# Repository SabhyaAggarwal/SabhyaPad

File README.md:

# SabhyaPad

This is my own MacroPad, called **SabhyaPad**! It has 6 buttons that can easily be customized using QMK. Using it is really simple: just plug a USB-C cable into your computer, allow it to connect, and then start using it.

I made this so that my life is easier. Currently, it is configured to do this...

## Here is a [video](https://youtu.be/60F119tDTQQ) of it on YouTube!!! I accidentally put the wrong link in the demo section actually...

## BOM
|Item                    |Quantity|Remarks                                       |Unit Price 1 (INR)|Order Quantity|Order Unit Price (INR)|Order Unit Price (Est. USD)|Link To Buy                                                                                                                           |
|------------------------|--------|----------------------------------------------|------------------|--------------|----------------------|---------------------------|--------------------------------------------------------------------------------------------------------------------------------------|
|Switches                |6       |Switches of MX style.                         |₹93.18            |6             |₹93.18                |$1.00                      |https://www.mouser.in/ProductDetail/CHERRY/MX1A-L1NN?qs=F5EMLAvA7IDlALNAurZTXA%3D%3D                                                  |
|Seeed Studio Xiao RP2040|1       |Main Chip.                                    |₹464.97           |1             |₹464.97               |$4.90                      |https://www.mouser.in/ProductDetail/Seeed-Studio/102010630?qs=sqEgtWRSLJ0HHL%252BkmwiGyA%3D%3D                                        |
|Blank DSA keycaps       |6       |Blank DSA keycaps of black colour(3d printed).|₹2.13             |6             |₹12.75                |$0.13                      |Own 3d printer or print-legion                                                                                                        |
|PCB                     |1       |Main PCB.                                     |₹1112.00          |1             |₹95.25                |$1.00                      |allpcb.com                                                                                                                            |
|M3x16mm screws          |4       |Screws.                                       |₹12.27            |4             |₹49.09                |$0.51                      |https://robokits.co.in/robot-parts/nut-bolts-standoffs/mushroom-head-bolts/m3-x-16-mm-ss-bolt-precision-stainless-steel-304-moq-25-pcs|
|M3 nuts                 |4       |Nuts                                          |₹1.18             |4             |₹4.72                 |$0.05                      |https://robokits.co.in/robot-parts/nut-bolts-standoffs/nuts/m3-nuts-304-stainless-steel-moq-50-pcs                                    |

## Hardware

This is the schematic of my PCB...

And this is what my PCB design looks like...

### 3D Render of PCB

## 3D Models

Please note that I will add USB-C port after I receive the PCB and can confirm the measurements

### Case Render(SabhyaPad Case Assembled)

### Cut Case Render(SabhyaPad Case Cut)

### Final Render(no keycaps)

---

# Assembly

For assembly:
1. 3D Print the case cut file.
2. Take your soldered PCB and push it into the top part. It will click and then it will be attached.
3. Take the bottom part and put it at the bottom.
4. Use M3x16mm screws and the M3 nuts to enclose it.

# Firmware

The SabhyaPad firmware is based on **QMK Firmware** and is located in:

```text
FIRMWARE/sabhyapad
```

## Requirements

Install **QMK MSYS** from:

https://qmk.fm

After installation, open QMK MSYS and verify it is installed correctly:

```bash
qmk --version
```

## Setting Up QMK

Clone and set up QMK Firmware:

```bash
qmk setup
```

## Installing SabhyaPad

Navigate to the keyboards directory:

```bash
cd qmk_firmware/keyboards
```

Clone this repository:

```bash
git clone https://github.com/SabhyaAggarwal/SabhyaPad.git
```

## Building the Firmware

Return to the QMK root directory:

```bash
cd ../..
```

Compile the firmware:

```bash
qmk compile -kb sabhyapad -km default
```

Or:

```bash
make sabhyapad:default
```

## Firmware Output

A successful build will generate:

```text
sabhyapad_default.uf2
```

Since SabhyaPad uses an **RP2040** microcontroller, the firmware is generated in UF2 format.

## Flashing the Firmware

1. Hold the **BOOTSEL** button while plugging the keyboard into your computer.
2. A drive named **RPI-RP2** will appear.
3. Drag and drop:

```text
sabhyapad_default.uf2
```

onto the drive.

The keyboard will automatically reboot and start running the new firmware.

## Updating

Pull the latest changes:

```bash
cd qmk_firmware/keyboards/SabhyaPad
git pull
```

Rebuild:

```bash
cd ../..
qmk compile -kb sabhyapad -km default
```

## Troubleshooting

Check your QMK installation:

```bash
qmk doctor
```

Clean and rebuild:

```bash
qmk clean
qmk compile -kb sabhyapad -km default
```

List available keymaps:

```bash
qmk list-keymaps -kb sabhyapad
```

## Quick Start

```bash
qmk setup

cd qmk_firmware/keyboards
git clone https://github.com/SabhyaAggarwal/SabhyaPad.git

cd ../..

qmk compile -kb sabhyapad -km default
```

### Specifications

- MCU: RP2040
- Switches: 6 Mechanical Switches
- Firmware: QMK
- Connector: USB-C
- Firmware Format: UF2

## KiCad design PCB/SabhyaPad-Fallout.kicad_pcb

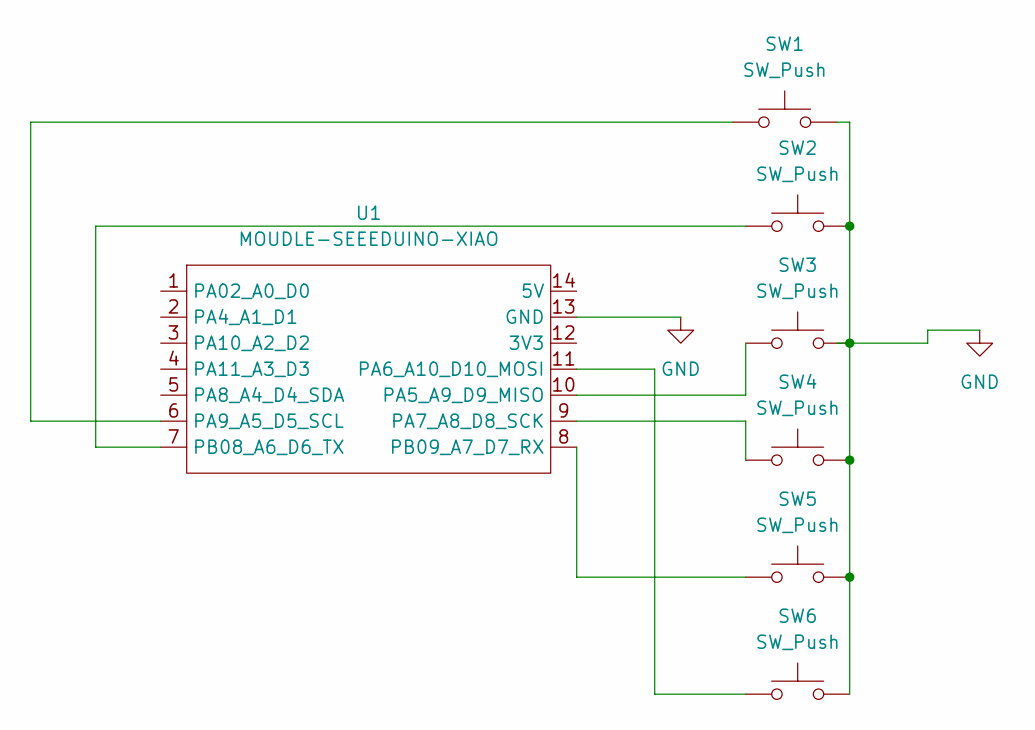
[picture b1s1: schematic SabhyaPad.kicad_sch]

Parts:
SW1, SW2, SW3, SW4, SW5, SW6: SW_Push; SW_Cherry_MX_1.00u_PCB
U1: MOUDLE-SEEEDUINO-XIAO; XIAO-Generic-Hybrid-14P-2.54-21X17.8MM

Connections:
GND: SW1.2, SW2.2, SW3.2, SW4.2, SW5.2, SW6.2, U1.13 (GND)
unnamed: SW3.1, U1.10 (PA5_A9_D9_MISO)
unnamed: SW6.1, U1.11 (PA6_A10_D10_MOSI)
unnamed: SW4.1, U1.9 (PA7_A8_D8_SCK)
unnamed: SW1.1, U1.6 (PA9_A5_D5_SCL)
unnamed: SW2.1, U1.7 (PB08_A6_D6_TX)
unnamed: SW5.1, U1.8 (PB09_A7_D7_RX)

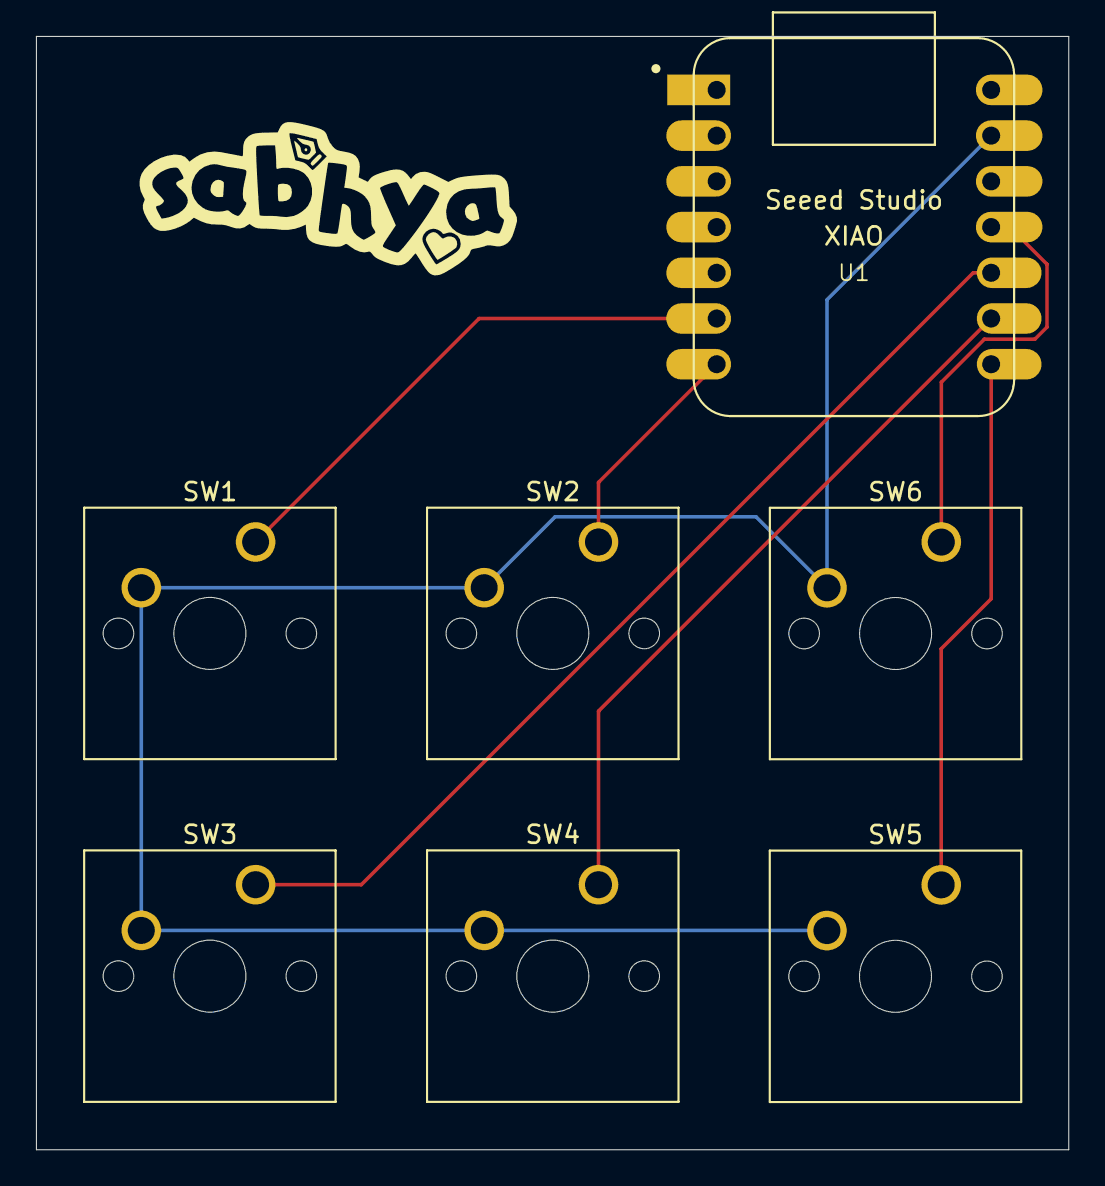
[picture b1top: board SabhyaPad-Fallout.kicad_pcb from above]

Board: 2 copper layers, 57.3 x 61.8 mm, 7 parts (0 on the bottom side), 7 nets.

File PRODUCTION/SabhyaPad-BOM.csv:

Customer Part No.,Quantity 1,Mfr Part Number (Input),Description (Input),Mfr Part Number,Mouser Part Number,Manufacturer Name,Description ,Unit Price 1 (INR),Order Quantity,Order Unit Price (INR)
"SW1,SW2,SW3,SW4,SW5,SW6",6,MX1A-L1NN,Button_Switch_Keyboard:SW_Cherry_MX_1.00u_PCB,MX1A-L1NN,540-MX1A-L1NN,CHERRY,"Pushbutton Switches Pushbutton Switches Red stem, Full travel, linear feel, low force spring, Red stem, Frame mount",₹93.18,6,₹93.18
U1,1,102010630,footprints:XIAO-Generic-Hybrid-14P-2.54-21X17.8MM,102010630,713-102010630,Seeed Studio,Development Boards & Kits - ARM Development Boards & Kits - ARM Seeed Studio XIAO RP2040 (Pre-Soldered),₹464.97,1,₹464.97
Blank DSA keycaps,6,-,Blank DSA keycaps,-,-,-,Blank DSA keycaps,₹100.00,6,₹600.00

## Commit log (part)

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2026-06-10 Fix CAD
2026-06-11 Update default keymap layout (volume, brightness, cmd+c/v) and rebuild firmware
2026-06-11 Add compressed project showcase video and gitignore
2026-06-23 Add Source files and case cut .stl file
